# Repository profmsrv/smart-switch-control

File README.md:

🏠 SmartHomePro
A smart home automation system built using ESP8266 and RS485 for reliable and scalable home control.

✨ Features
Wi-Fi based device control
ESP8266 based controllers
RS485 communication
Mobile and Web control
Physical switch control
Energy monitoring
Optional Firebase cloud integration
Secure user authentication
Scalable relay control
Local hotspot mode
⚙️ Technology
Microcontroller: ESP8266
Communication: RS485
Cloud: Firebase
Connectivity: Wi-Fi
Control: Mobile, Web & Physical Switches
🏗️ How It Works
The main ESP8266 controller communicates with multiple sub-controllers using RS485. Each sub-controller controls connected electrical loads through relays.

Mobile / Web
│
Wi-Fi
│
Main Controller
ESP8266
│
RS485
│
┌───┼────┬────┐
│ │ │ │
Sub Sub Sub Sub
│ │ │ │
Relay Relay Relay Relay
│ │ │ │
Loads Loads Loads Loads
⚡ Energy Monitoring
Monitor current and power consumption of connected electrical loads to understand usage and improve energy efficiency.

☁️ Firebase
Optional Firebase integration allows remote control, authentication, and real-time system monitoring from anywhere.

🚀 Getting Started
Clone this repository.
Open the ESP8266 project in Arduino IDE.
Install the required libraries.
Configure Wi-Fi and Firebase settings.
Upload the firmware to the ESP8266.
Connect the controllers using RS485.
Connect and configure the relay outputs.
⚠️ Safety
This project may involve high-voltage electrical systems. Electrical wiring and installation should only be performed by a qualified professional.

📌 Project Status
🚧 Under Development

❤️ About
SmartHomePro is designed to provide reliable, scalable, and energy-efficient smart home automation using affordable embedded hardware.

Made with ❤️ in India 🇮🇳

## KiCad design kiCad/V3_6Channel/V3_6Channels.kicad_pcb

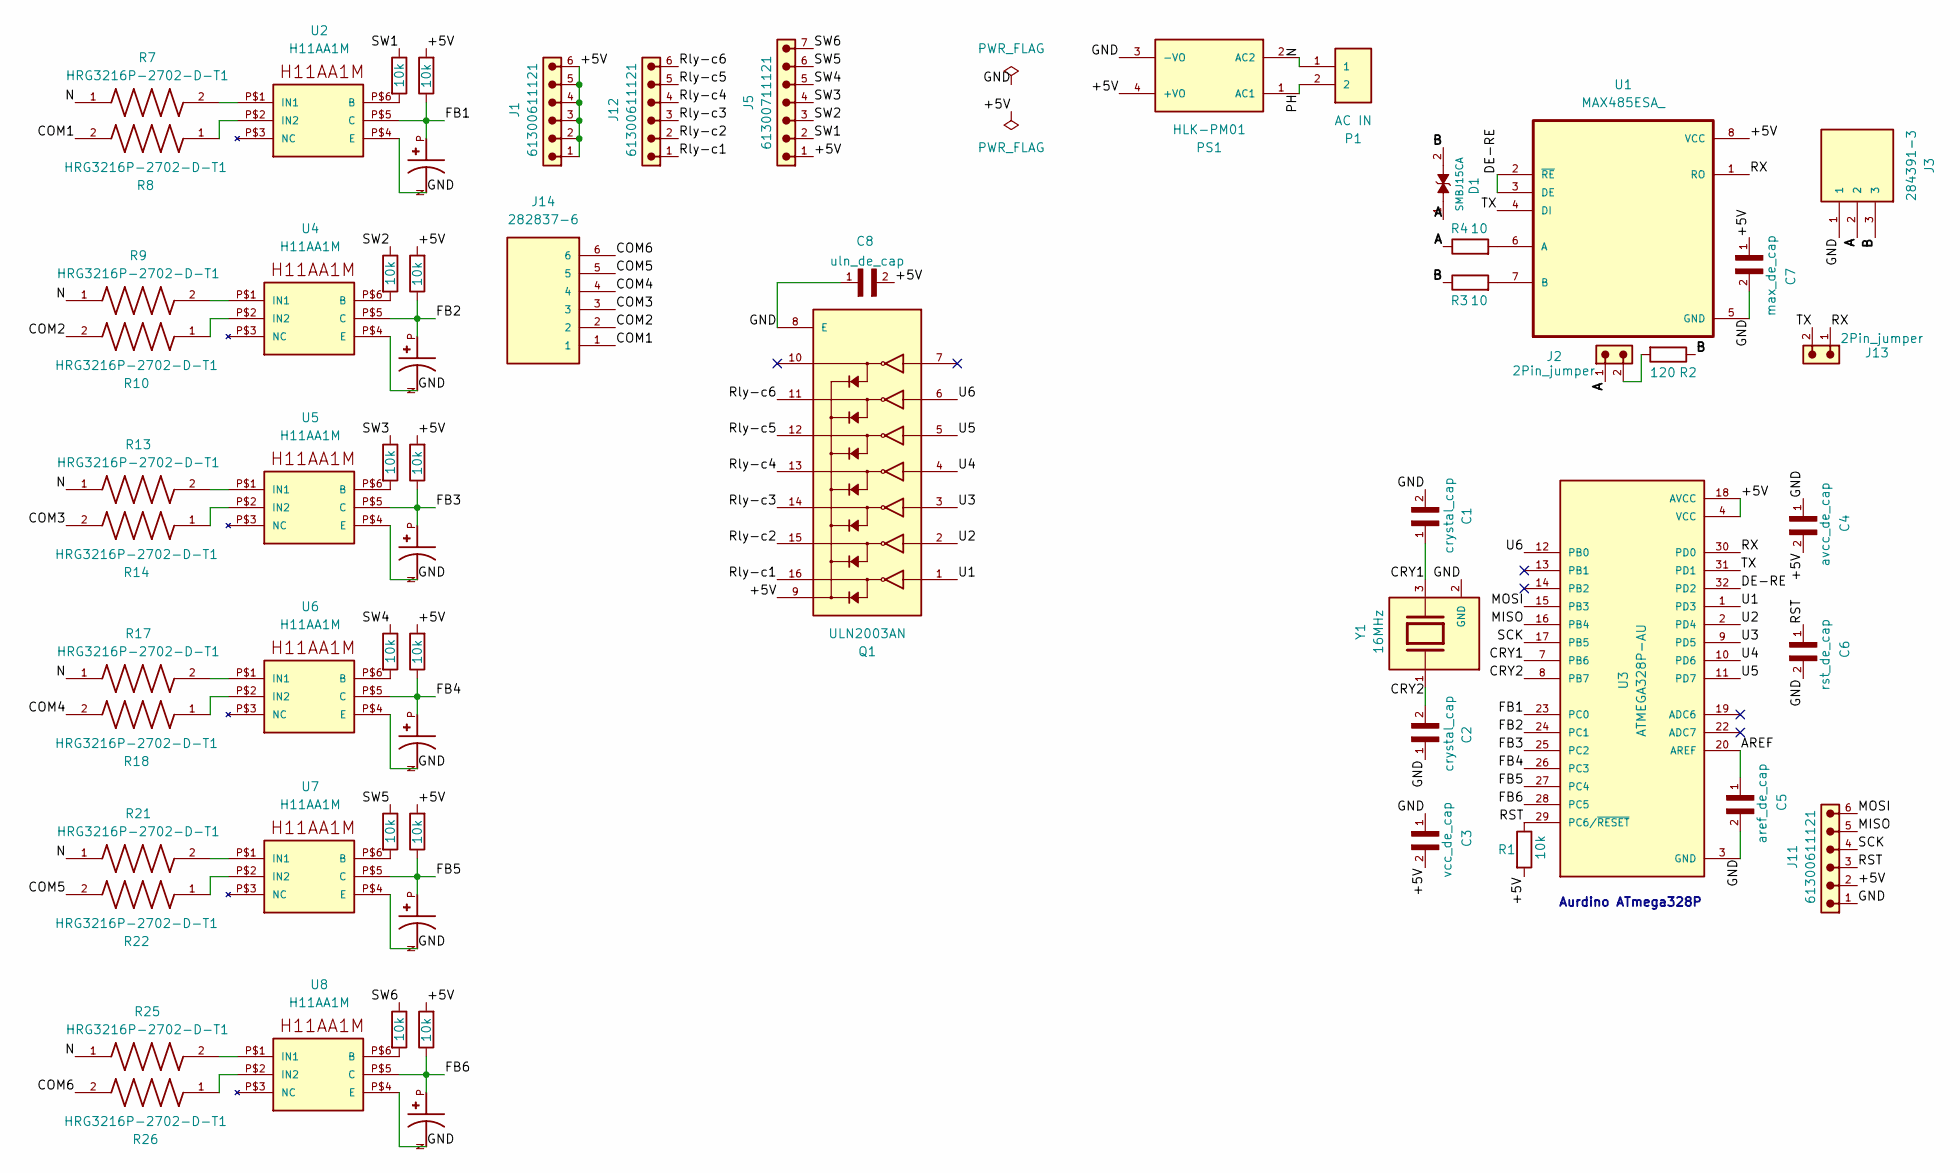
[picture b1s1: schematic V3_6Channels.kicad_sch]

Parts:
C1, C2: crystal_cap; CAPC1608X90
C3: vcc_de_cap; CAPC1005X55N; PARTREV Jul. 2024
C4: avcc_de_cap; CAPC1005X55N; PARTREV Jul. 2024
C5: aref_de_cap; CAPC1005X55N; PARTREV Jul. 2024
C6: rst_de_cap; CAPC1005X55N; PARTREV Jul. 2024
C7: max_de_cap; CAPC1005X55N; PARTREV Jul. 2024
C8: uln_de_cap; CAPC1005X55N; PARTREV Jul. 2024
C9, C10, C11, C12, C13, C14: AC Ripple Filter; CAPAE530X565N; PARTREV 7/13/2023
D1: SMBJ15CA; DIOM4336X265N; PARTREV I2102
J1, J11, J12: 61300611121
J2, J13: 2Pin_jumper; 61300211121
J3: 284391-3; TE_284391-3; PARTREV R
J5: 61300711121
J14: 282837-6; TE_282837-6; PARTREV R
P1: AC IN; TE_282837-2; PARTREV G3
PS1: HLK-PM01; CONV_HLK-PM01
Q1: ULN2003AN; DIP794W45P254L1969H508Q16; PARTREV P
R1, R5, R6, R11, R12, R15, R16, R19, R20, R23, R24, R27, R28: 10k; RESC2012X65N
R2: 120; RESC3216X70N
R3, R4: 10; RESC2012X60N
R7, R8, R9, R10, R13, R14, R17, R18, R21, R22, R25, R26: HRG3216P-2702-D-T1; RESC3216X55N
U1: MAX485ESA_; SOIC127P600X175-8N
U2, U4, U5, U6, U7, U8: H11AA1M; DIP6
U3: ATMEGA328P-AU; QFP80P900X900X120-32N; PARTREV 8271A
Y1: 16MHz; XTAL_ABM8-16.000MHz-D1X-T; PARTREV 44041

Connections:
/A: D1.1, J2.1, J3.2, R4.1
/AREF: C5.1, U3.20 (AREF)
/B: D1.2, J3.3, R2.1, R3.1
/COM1: J14.1, R8.2
/COM2: J14.2, R10.2
/COM3: J14.3, R14.2
/COM4: J14.4, R18.2
/COM5: J14.5, R22.2
/COM6: J14.6, R26.2
/CRY1: C1.1, U3.7 (PB6), Y1.3
/CRY2: C2.2, U3.8 (PB7), Y1.1
/DE-RE: U1.2 (~RE), U1.3 (DE), U3.32 (PD2)
/FB1: C9.P, R5.1, U2.P$5 (C), U3.23 (PC0)
/FB2: C10.P, R12.1, U3.24 (PC1), U4.P$5 (C)
/FB3: C11.P, R16.1, U3.25 (PC2), U5.P$5 (C)
/FB4: C12.P, R20.1, U3.26 (PC3), U6.P$5 (C)
/FB5: C13.P, R24.1, U3.27 (PC4), U7.P$5 (C)
/FB6: C14.P, R28.1, U3.28 (PC5), U8.P$5 (C)
/MISO: J11.5, U3.16 (PB4)
/MOSI: J11.6, U3.15 (PB3)
/N: P1.1, PS1.2 (AC2), R7.1, R9.1, R13.1, R17.1, R21.1, R25.1
/PH: P1.2, PS1.1 (AC1)
/RST: C6.1, J11.3, R1.1, U3.29 (PC6/~RESET)
/RX: J13.1, U1.1 (RO), U3.30 (PD0)
/Rly-c1: J12.1, Q1.16
/Rly-c2: J12.2, Q1.15
/Rly-c3: J12.3, Q1.14
/Rly-c4: J12.4, Q1.13
/Rly-c5: J12.5, Q1.12
/Rly-c6: J12.6, Q1.11
/SCK: J11.4, U3.17 (PB5)
/SW1: J5.2, R6.1
/SW2: J5.3, R11.1
/SW3: J5.4, R15.1
/SW4: J5.5, R19.1
/SW5: J5.6, R23.1
/SW6: J5.7, R27.1
/TX: J13.2, U1.4 (DI), U3.31 (PD1)
/U1: Q1.1, U3.1 (PD3)
/U2: Q1.2, U3.2 (PD4)
/U3: Q1.3, U3.9 (PD5)
/U4: Q1.4, U3.10 (PD6)
/U5: Q1.5, U3.11 (PD7)
/U6: Q1.6, U3.12 (PB0)
GND: C1.2, C2.1, C3.1, C4.1, C5.2, C6.2, C7.2, C8.1, C9.N, C10.N, C11.N, C12.N, C13.N, C14.N, J3.1, J11.1, PS1.3 (-VO), Q1.8 (E), U1.5 (GND), U2.P$4 (E), U3.3 (GND), U3.5 (GND), U3.21 (GND), U4.P$4 (E), U5.P$4 (E), U6.P$4 (E), U7.P$4 (E), U8.P$4 (E), Y1.2 (GND), Y1.4 (GND)
unnamed: J2.2, R2.2
unnamed: R4.2, U1.6 (A)
unnamed: R3.2, U1.7 (B)
unnamed: R6.2, U2.P$6 (B)
unnamed: R7.2, U2.P$1 (IN1)
unnamed: R8.1, U2.P$2 (IN2)
unnamed: R11.2, U4.P$6 (B)
unnamed: R9.2, U4.P$1 (IN1)
unnamed: R10.1, U4.P$2 (IN2)
unnamed: R15.2, U5.P$6 (B)
unnamed: R13.2, U5.P$1 (IN1)
unnamed: R14.1, U5.P$2 (IN2)
unnamed: R19.2, U6.P$6 (B)
unnamed: R17.2, U6.P$1 (IN1)
unnamed: R18.1, U6.P$2 (IN2)
unnamed: R23.2, U7.P$6 (B)
unnamed: R21.2, U7.P$1 (IN1)
unnamed: R22.1, U7.P$2 (IN2)
unnamed: R27.2, U8.P$6 (B)
unnamed: R25.2, U8.P$1 (IN1)
unnamed: R26.1, U8.P$2 (IN2)
VCC: C3.2, C4.2, C7.1, C8.2, J1.1, J1.2, J1.3, J1.4, J1.5, J1.6, J5.1, J11.2, PS1.4 (+VO), Q1.9, R1.2, R5.2, R12.2, R16.2, R20.2, R24.2, R28.2, U1.8 (VCC), U3.4 (VCC), U3.6 (VCC), U3.18 (AVCC)

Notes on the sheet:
Aurdino ATmega328P

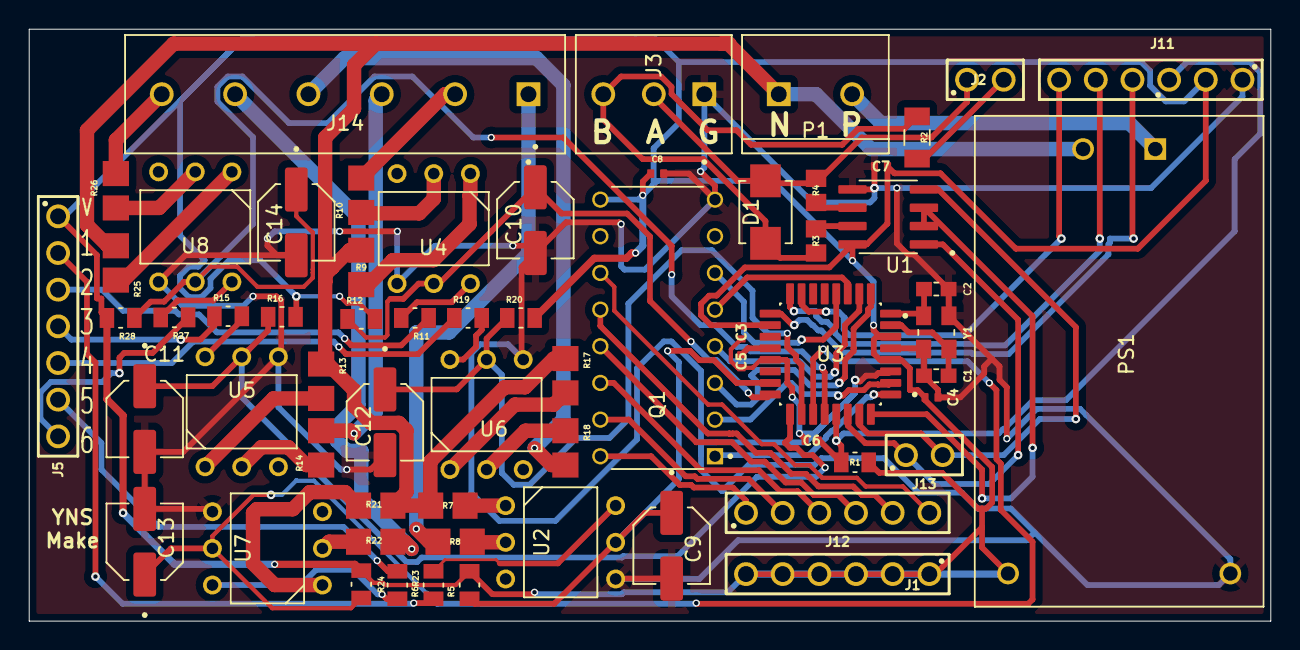
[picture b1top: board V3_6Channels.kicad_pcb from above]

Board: 2 copper layers, 86.0 x 41.0 mm, 63 parts (0 on the bottom side), 67 nets.
